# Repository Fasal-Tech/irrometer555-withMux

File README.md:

# Watermark irrometer-555withMux
This repository contains the PCB design files to interface the popular Irrometer 200SS soil moisture sensor and read the equivalent soil tension in Frequency.

The RT9193-33GB IC is an LDO used to convert 5V to 3.3V for LMC555 and 74HC4052D ICs. Using the ENABLE pin of the LDO, we can control the poweron-off of the circuit. It is a LDO with drop voltage of around 0.3V. SO your board supply VCC can go as low as 3.6V and the circuit will still function.

The Frequency to KPa (CB) conversion is as below: <br>
```
kPa = 0                             for Hz > 6430
kPa = 9 - (Hz - 4600) * 0.004286    for 4330 <= Hz <= 6430
kPa = 15 - (Hz - 2820) * 0.003974   for 2820 <= Hz <= 4330
kPa = 35 - (Hz - 1110) * 0.01170    for 1110 <= Hz <= 2820
kPa = 55 - (Hz - 770) * 0.05884     for 770 <= Hz <= 1110
kPa = 75 - (Hz - 600) * 0.1176      for 600 <= Hz <= 770
kPa = 100 - (Hz - 485) * 0.2174     for 485 <= Hz <= 600
kPa = 200 - (Hz - 293) * 0.5208     for 293 <= Hz <= 485
kPa = 200                           for Hz < 293
```

You can achieve this in the microcontroller program using "If" conditions. The conversion reference is from the datasheet of SMX circuit (https://www.emesystems.com/smx/documents/SMX_2018.pdf)

The attached Arduino code is tested successfully with ATmega328p and STM32F103 microcontrollers. Same can be adapted to PIC controllers and others as well.

Read more here - https://medium.com/fasal-engineering/a-low-cost-circuit-to-read-from-multiple-watermark-irrometer-200ss-sensors-a4c838da233a

# Liscense
MIT 

# Warranty
THE SOFTWARE AND HARDWARE FILES ARE PROVIDED "AS IS", WITHOUT WARRANTY OF ANY KIND, EXPRESS OR
IMPLIED, INCLUDING BUT NOT LIMITED TO THE WARRANTIES OF MERCHANTABILITY,
FITNESS FOR A PARTICULAR PURPOSE AND NONINFRINGEMENT. IN NO EVENT SHALL THE
AUTHORS OR COPYRIGHT HOLDERS BE LIABLE FOR ANY CLAIM, DAMAGES OR OTHER
LIABILITY, WHETHER IN AN ACTION OF CONTRACT, TORT OR OTHERWISE, ARISING FROM,
OUT OF OR IN CONNECTION WITH THE SOFTWARE OR THE USE OR OTHER DEALINGS IN THE
SOFTWARE AND OR HARDWARE.

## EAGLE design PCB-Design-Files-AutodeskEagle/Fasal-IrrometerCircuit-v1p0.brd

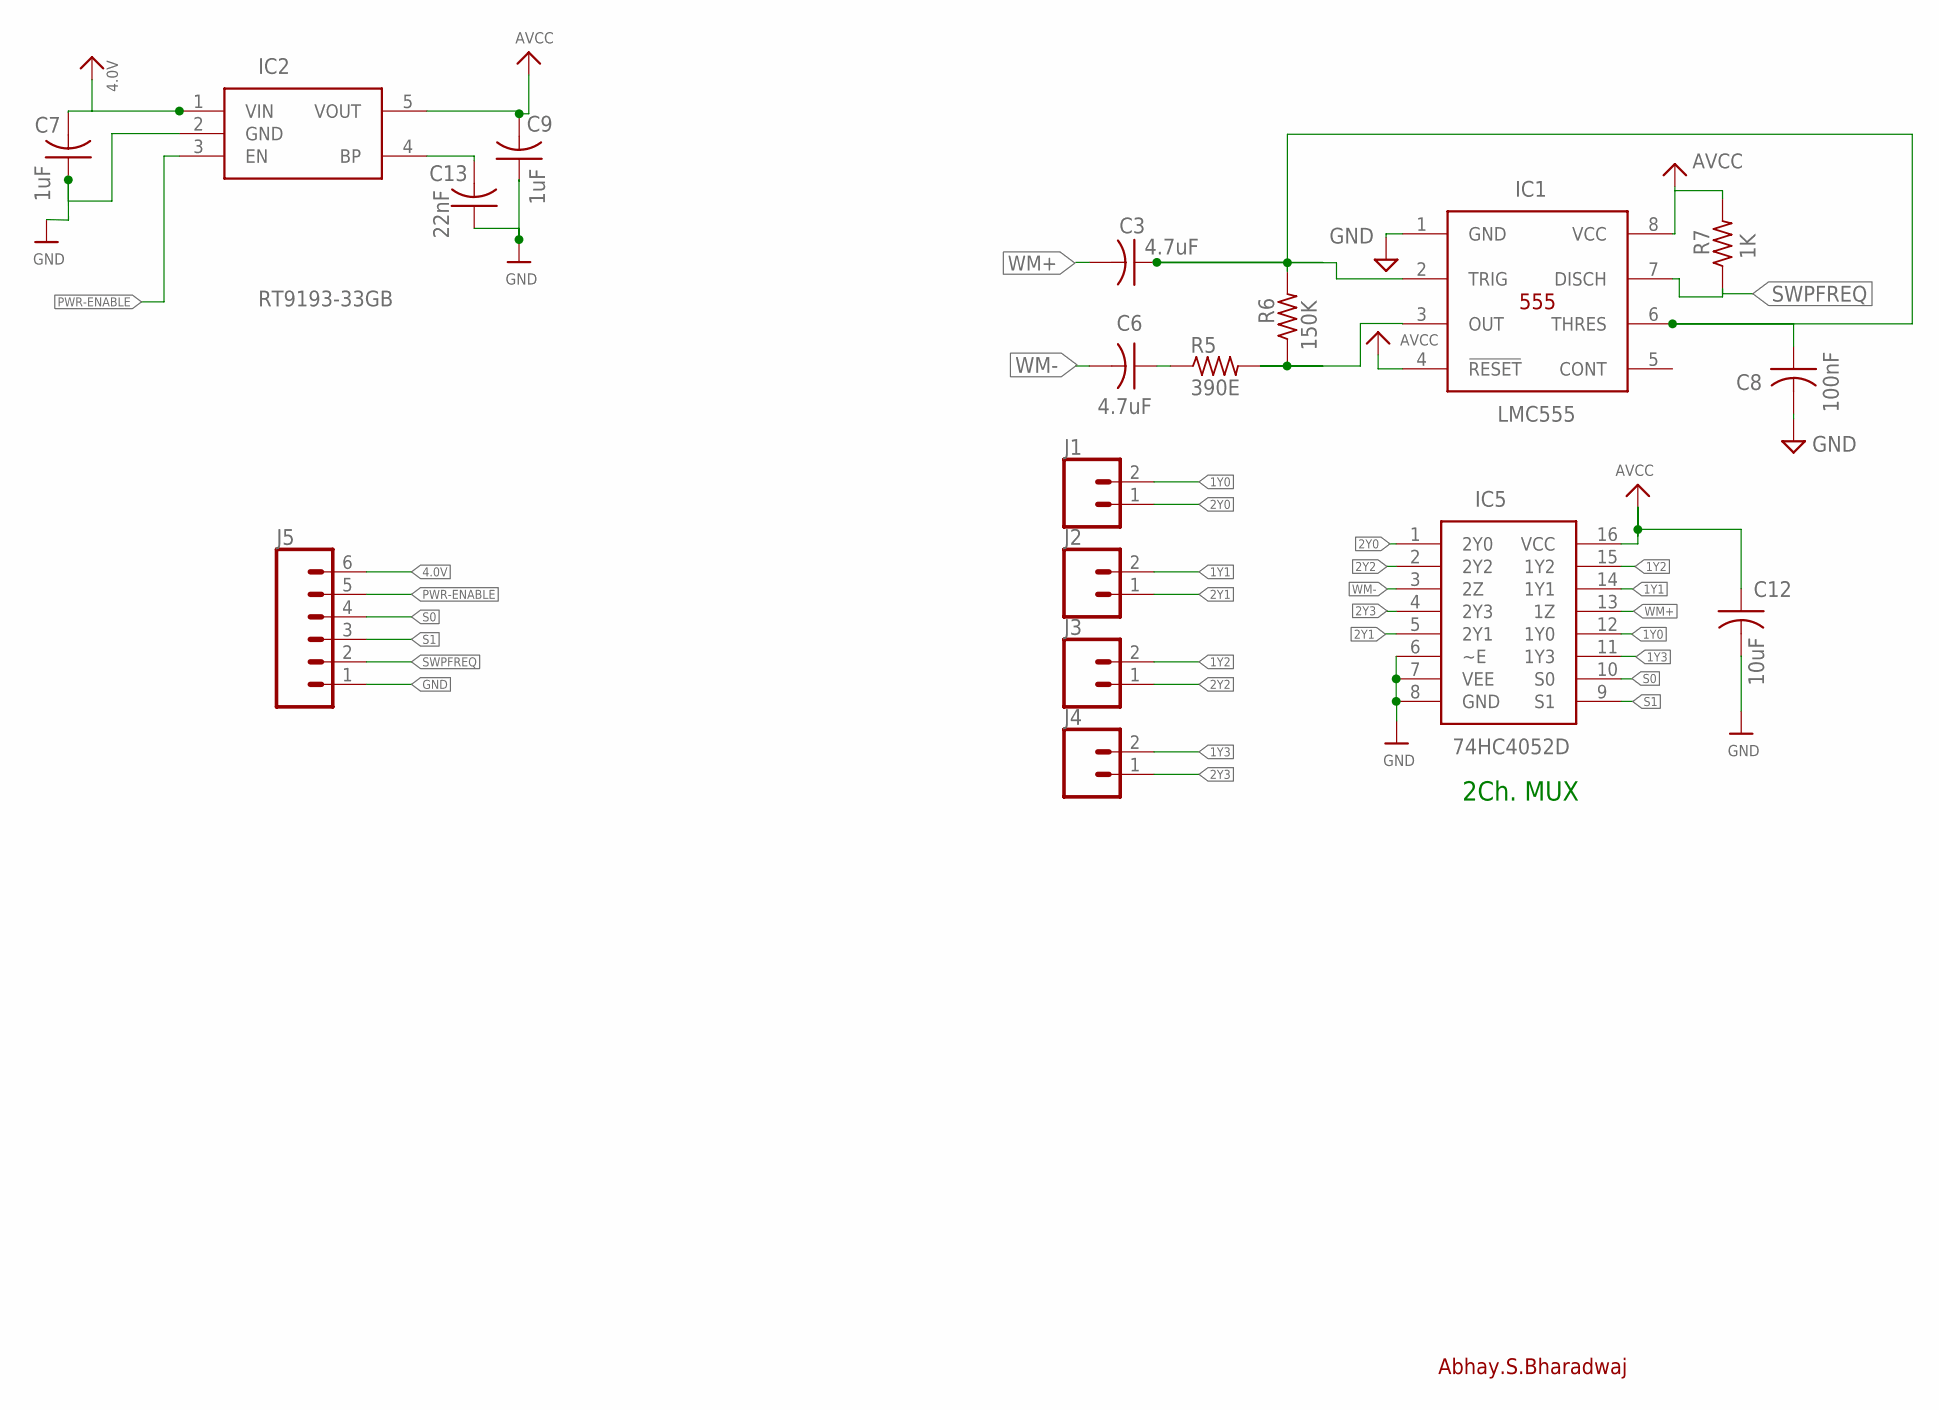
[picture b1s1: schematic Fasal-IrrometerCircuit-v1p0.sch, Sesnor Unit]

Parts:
C3, C6: 4.7uF; C0603K
C7, C9: 1uF; C0603K
C8: 100nF; C0603K
C12: 10uF; C0603K
C13: 22nF; C0603K
IC1: LMC555; SOIC127P600X175-8N
IC2: RT9193-33GB; SOT94P279X130-5N
IC5: 74HC4052D; SOIC127P600X175-16N
J1, J2, J3, J4: CONN_023.5MM; SCREWTERMINAL-3.5MM-2
J5: CONN_06POLAR; MOLEX-1X6
R5: 390E; R0603
R6: 150K; R0603
R7: 1K; R0603

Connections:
1Y0: IC5.12 (1Y0), J1.2
1Y1: IC5.14 (1Y1), J2.2
1Y2: IC5.15 (1Y2), J3.2
1Y3: IC5.11 (1Y3), J4.2
2Y0: IC5.1 (2Y0), J1.1
2Y1: IC5.5 (2Y1), J2.1
2Y2: IC5.2 (2Y2), J3.1
2Y3: IC5.4 (2Y3), J4.1
4.0V: C7.2, IC2.1 (VIN), J5.6
AVCC: C9.2, C12.1, IC1.4 (!RESET), IC1.8 (VCC), IC2.5 (VOUT), IC5.16 (VCC), R7.2
GND: C7.1, C8.2, C9.1, C12.2, C13.1, IC1.1 (GND), IC2.2 (GND), IC5.6 (~E), IC5.7 (VEE), IC5.8 (GND), J5.1
unnamed: IC1.3 (OUT), R5.2, R6.1
unnamed: C3.1, C8.1, IC1.2 (TRIG), IC1.6 (THRES), R6.2
unnamed: C6.1, R5.1
unnamed: C13.2, IC2.4 (BP)
PWR-ENABLE: IC2.3 (EN), J5.5
S0: IC5.10 (S0), J5.4
S1: IC5.9 (S1), J5.3
SWPFREQ: IC1.7 (DISCH), J5.2, R7.1
WM+: C3.2, IC5.13 (1Z)
WM-: C6.2, IC5.3 (2Z)

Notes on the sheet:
Abhay.S.Bharadwaj
2Ch. MUX

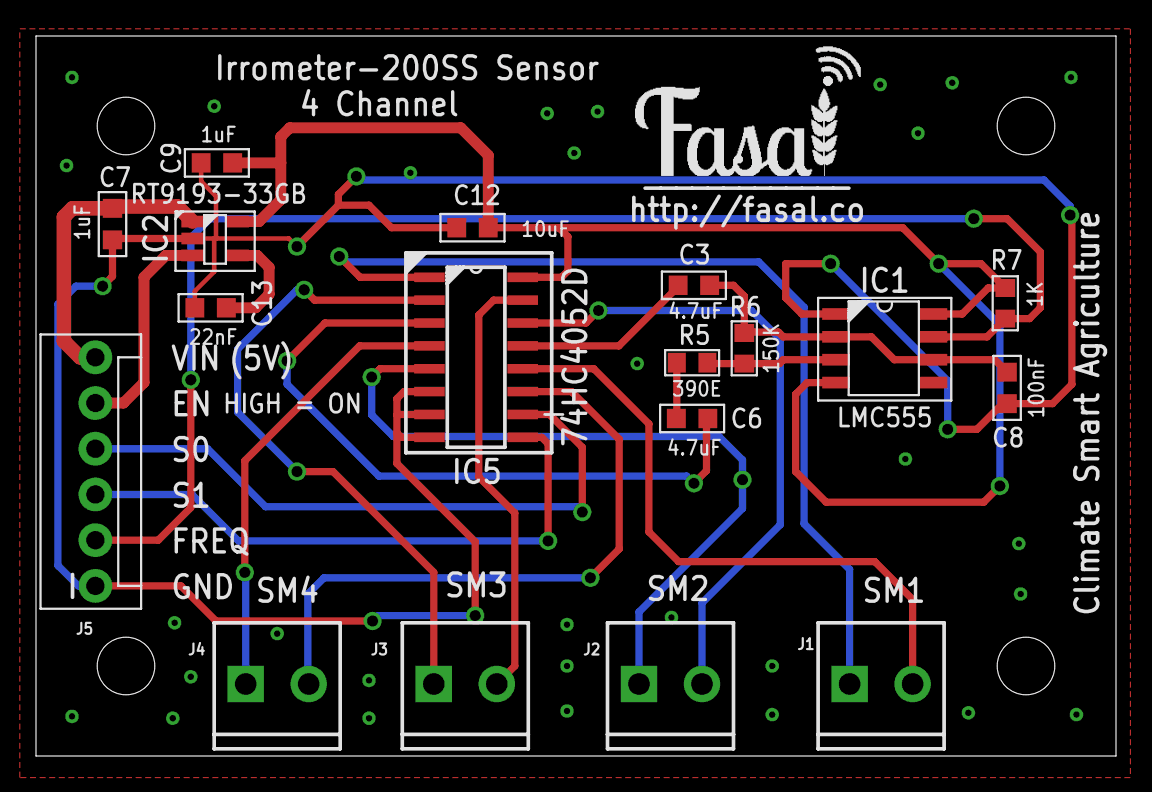
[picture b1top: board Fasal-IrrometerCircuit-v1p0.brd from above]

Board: 2 copper layers, 60.0 x 40.0 mm, 18 parts (0 on the bottom side), 21 nets.

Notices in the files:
parts and their libraries:
SparkFun-Connectors: Licensing: Creative Commons ShareAlike 4.0 International - https://creativecommons.org/licenses/by-sa/4.0
cap-smd-0805: This work is placed in the public domain, and may be freely used for commercial and non-commercial work with the following conditions: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
